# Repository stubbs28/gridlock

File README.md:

# gridlock
custom handmade keyboard

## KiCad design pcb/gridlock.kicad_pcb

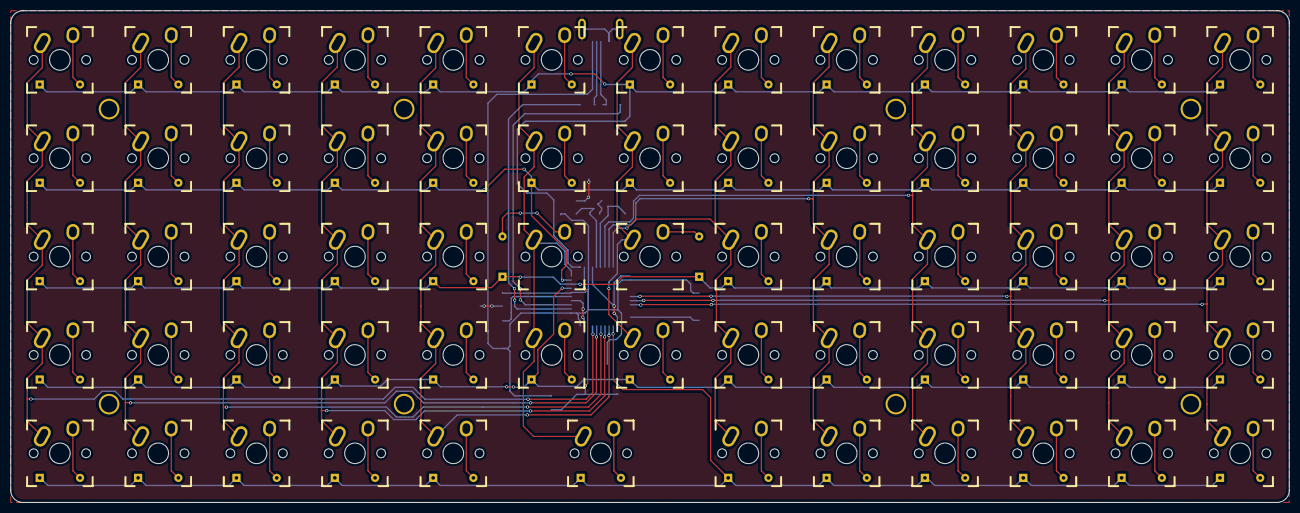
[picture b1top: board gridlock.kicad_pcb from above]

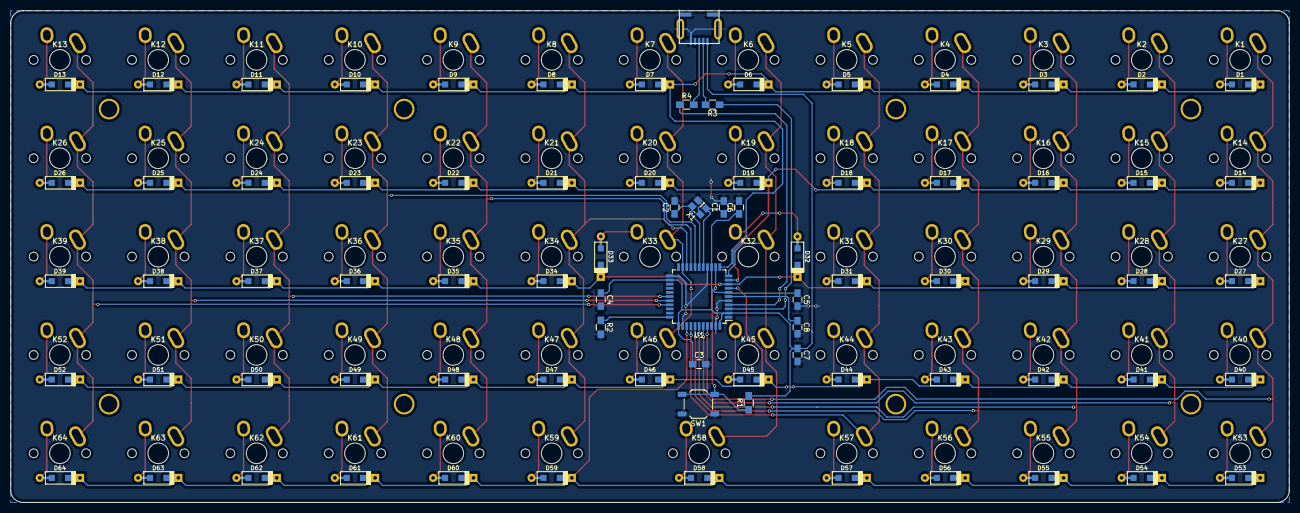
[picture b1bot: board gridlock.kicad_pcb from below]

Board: 2 copper layers, 247.7 x 95.2 mm, 152 parts (80 on the bottom side), 93 nets.

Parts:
C1, C2: 22p; C_0805_HandSoldering
C3, C4, C5, C6: 0.1u; C_0805_HandSoldering
C7: 4.7u; C_0805_HandSoldering
C8: 1u; C_0805_HandSoldering
D1, D2, D3, D4, D5, D6, D7, D8, D9, D10, D11, D12, D13, D14, D15, D16, D17, D18, D19, D20, D21, D22, D23, D24, D25, D26, D27, D28, D29, D30, D31, D32, D33, D34, D35, D36, D37, D38, D39, D40, D41, D42, D43, D44, D45, D46, D47, D48, D49, D50, D51, D52, D53, D54, D55, D56, D57, D58, D59, D60, D61, D62, D63, D64: D; D_SOD123_axial
HOLE_M3, HOLE_M3#2, HOLE_M3#3, HOLE_M3#4, HOLE_M3#5, HOLE_M3#6, HOLE_M3#7, HOLE_M3#8: VAL**; HOLE_M3
J1: USB_mini_micro_B; USB_miniB_hirose_5S8
K1, K2, K3, K4, K5, K6, K7, K8, K9, K10, K11, K12, K13, K14, K15, K16, K17, K18, K19, K20, K21, K22, K23, K24, K25, K26, K27, K28, K29, K30, K31, K32, K33, K34, K35, K36, K37, K38, K39, K40, K41, K42, K43, K44, K45, K46, K47, K48, K49, K50, K51, K52, K53, K54, K55, K56, K57, K58, K59, K60, K61, K62, K63, K64: KEYSW; Mx_Alps_100
R1, R2: 10k; R_0805_HandSoldering
R3, R4: 22; R_0805_HandSoldering
SW1: SW_PUSH; SW_SPST_TL3342
U1: ATMEGA32U4; TQFP-44_10x10mm_Pitch0.8mm
X1: XTAL_GND; crystal_FA238_TSX3225

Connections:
/col0: K1.1, K14.1, K27.1, K40.1, K53.1, U1.41
/col1: K2.1, K15.1, K28.1, K41.1, K54.1, U1.40
/col2: K3.1, K16.1, K29.1, K42.1, K55.1, U1.39
/col3: K4.1, K17.1, K30.1, K43.1, K56.1, U1.38
/col4: K5.1, K18.1, K31.1, K44.1, K57.1, U1.37
/col5: K6.1, K19.1, K32.1, K45.1, K58.1, U1.11
/col6: K7.1, K20.1, K33.1, K46.1, U1.21
/col7: K8.1, K21.1, K34.1, K47.1, K59.1, U1.20
/col8: K9.1, K22.1, K35.1, K48.1, K60.1, U1.19
/col9: K10.1, K23.1, K36.1, K49.1, K61.1, U1.18
/col10: K11.1, K24.1, K37.1, K50.1, K62.1, U1.28
/col11: K12.1, K25.1, K38.1, K51.1, K63.1, U1.29
/col12: K13.1, K26.1, K39.1, K52.1, K64.1, U1.30
/row0: D1.1, D2.1, D3.1, D4.1, D5.1, D6.1, D7.1, D8.1, D9.1, D10.1, D11.1, D12.1, D13.1, U1.12
/row1: D14.1, D15.1, D16.1, D17.1, D18.1, D19.1, D20.1, D21.1, D22.1, D23.1, D24.1, D25.1, D26.1, U1.10
/row2: D27.1, D28.1, D29.1, D30.1, D31.1, D32.1, D33.1, D34.1, D35.1, D36.1, D37.1, D38.1, D39.1, U1.9
/row3: D40.1, D41.1, D42.1, D43.1, D44.1, D45.1, D46.1, D47.1, D48.1, D49.1, D50.1, D51.1, D52.1, U1.8
/row4: D53.1, D54.1, D55.1, D56.1, D57.1, D58.1, D59.1, D60.1, D61.1, D62.1, D63.1, D64.1, U1.36
GND: C1.2, C2.2, C3.2, C4.2, C5.2, C6.2, C7.2, C8.2, J1.5, J1.6, R2.2, SW1.1, U1.5, U1.15, U1.23, U1.35, U1.43, X1.3
unnamed: C1.1, U1.16, X1.1
unnamed: C2.1, U1.17, X1.2
unnamed: C8.1, U1.6
unnamed: D1.2, K1.2
unnamed: D2.2, K2.2
unnamed: D3.2, K3.2
unnamed: D4.2, K4.2
unnamed: D5.2, K5.2
unnamed: D6.2, K6.2
unnamed: D7.2, K7.2
unnamed: D8.2, K8.2
unnamed: D9.2, K9.2
unnamed: D10.2, K10.2
unnamed: D11.2, K11.2
unnamed: D12.2, K12.2
unnamed: D13.2, K13.2
unnamed: D14.2, K14.2
unnamed: D15.2, K15.2
unnamed: D16.2, K16.2
unnamed: D17.2, K17.2
unnamed: D18.2, K18.2
unnamed: D19.2, K19.2
unnamed: D20.2, K20.2
unnamed: D21.2, K21.2
unnamed: D22.2, K22.2
unnamed: D23.2, K23.2
unnamed: D24.2, K24.2
unnamed: D25.2, K25.2
unnamed: D26.2, K26.2
unnamed: D27.2, K27.2
unnamed: D28.2, K28.2
unnamed: D29.2, K29.2
unnamed: D30.2, K30.2
unnamed: D31.2, K31.2
unnamed: D32.2, K32.2
unnamed: D33.2, K33.2
unnamed: D34.2, K34.2
unnamed: D35.2, K35.2
unnamed: D36.2, K36.2
unnamed: D37.2, K37.2
unnamed: D38.2, K38.2
unnamed: D39.2, K39.2
unnamed: D40.2, K40.2
unnamed: D41.2, K41.2
unnamed: D42.2, K42.2
unnamed: D43.2, K43.2
unnamed: D44.2, K44.2
unnamed: D45.2, K45.2
unnamed: D46.2, K46.2
unnamed: D47.2, K47.2
unnamed: D48.2, K48.2
unnamed: D49.2, K49.2
unnamed: D50.2, K50.2
unnamed: D51.2, K51.2
unnamed: D52.2, K52.2
unnamed: D53.2, K53.2
unnamed: D54.2, K54.2
unnamed: D55.2, K55.2
unnamed: D56.2, K56.2
unnamed: D57.2, K57.2
unnamed: D58.2, K58.2
unnamed: D59.2, K59.2
unnamed: D60.2, K60.2
unnamed: D61.2, K61.2
unnamed: D62.2, K62.2
unnamed: D63.2, K63.2
unnamed: D64.2, K64.2
unnamed: J1.2, R3.2
unnamed: J1.3, R4.2
unnamed: R1.1, SW1.2, U1.13
unnamed: R2.1, U1.33
unnamed: R3.1, U1.3
unnamed: R4.1, U1.4
VCC: C3.1, C4.1, C5.1, C6.1, C7.1, J1.1, R1.2, U1.2, U1.7, U1.14, U1.24, U1.34, U1.44

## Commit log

2018-08-08 init commit
